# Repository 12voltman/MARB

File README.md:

# MARB
Manual Audio Routing Board for channel muxing

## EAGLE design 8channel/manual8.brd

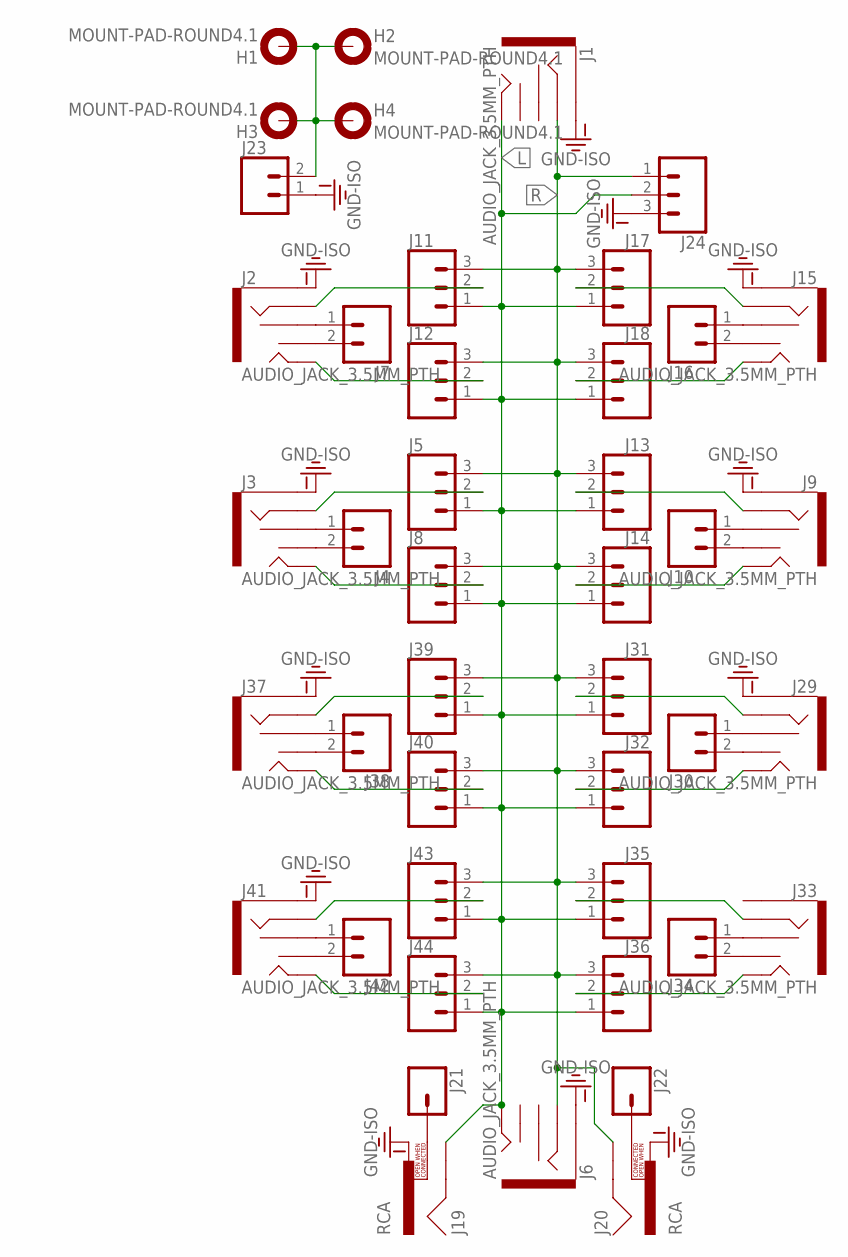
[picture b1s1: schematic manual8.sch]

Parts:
H1, H2, H3, H4: MOUNT-PAD-ROUND4.1; 4,1-PAD
J1, J2, J3, J6, J9, J15, J29, J33, J37, J41: AUDIO_JACK_3.5MM_PTH; AUDIO-JACK
J4, J7, J10, J16, J23, J30, J34, J38, J42: CONN_02; 1X02
J5, J8, J11, J12, J13, J14, J17, J18, J24, J31, J32, J35, J36, J39, J40, J43, J44: CONN_03; 1X03
J19, J20: RCA
J21, J22: CONN_01; 1X01

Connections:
GND-ISO: J1.SLEEVE, J2.SLEEVE, J3.SLEEVE, J6.SLEEVE, J9.SLEEVE, J15.SLEEVE, J19.PIN, J20.PIN, J23.1, J24.3, J29.SLEEVE, J33.SLEEVE, J37.SLEEVE, J41.SLEEVE
L: J1.TIP, J5.1, J6.TIP, J8.1, J11.1, J12.1, J13.1, J14.1, J17.1, J18.1, J19.SHELL, J24.2, J31.1, J32.1, J35.1, J36.1, J39.1, J40.1, J43.1, J44.1
unnamed: J2.RSH, J7.1
unnamed: J2.TSH, J7.2
unnamed: J2.RING, J11.2
unnamed: J2.TIP, J12.2
unnamed: J3.RSH, J4.1
unnamed: J3.TSH, J4.2
unnamed: J3.RING, J5.2
unnamed: J3.TIP, J8.2
unnamed: J9.RSH, J10.1
unnamed: J9.TSH, J10.2
unnamed: J9.RING, J13.2
unnamed: J9.TIP, J14.2
unnamed: J15.RSH, J16.1
unnamed: J15.TSH, J16.2
unnamed: J15.RING, J17.2
unnamed: J15.TIP, J18.2
unnamed: J19.SWITCH, J21.1
unnamed: J20.SWITCH, J22.1
unnamed: H1.B4,1, H2.B4,1, H3.B4,1, H4.B4,1, J23.2
unnamed: J29.RSH, J30.1
unnamed: J29.TSH, J30.2
unnamed: J29.RING, J31.2
unnamed: J29.TIP, J32.2
unnamed: J33.RSH, J34.1
unnamed: J33.TSH, J34.2
unnamed: J33.RING, J35.2
unnamed: J33.TIP, J36.2
unnamed: J37.RSH, J38.1
unnamed: J37.TSH, J38.2
unnamed: J37.RING, J39.2
unnamed: J37.TIP, J40.2
unnamed: J41.RSH, J42.1
unnamed: J41.TSH, J42.2
unnamed: J41.RING, J43.2
unnamed: J41.TIP, J44.2
R: J1.RING, J5.3, J6.RING, J8.3, J11.3, J12.3, J13.3, J14.3, J17.3, J18.3, J20.SHELL, J24.1, J31.3, J32.3, J35.3, J36.3, J39.3, J40.3, J43.3, J44.3

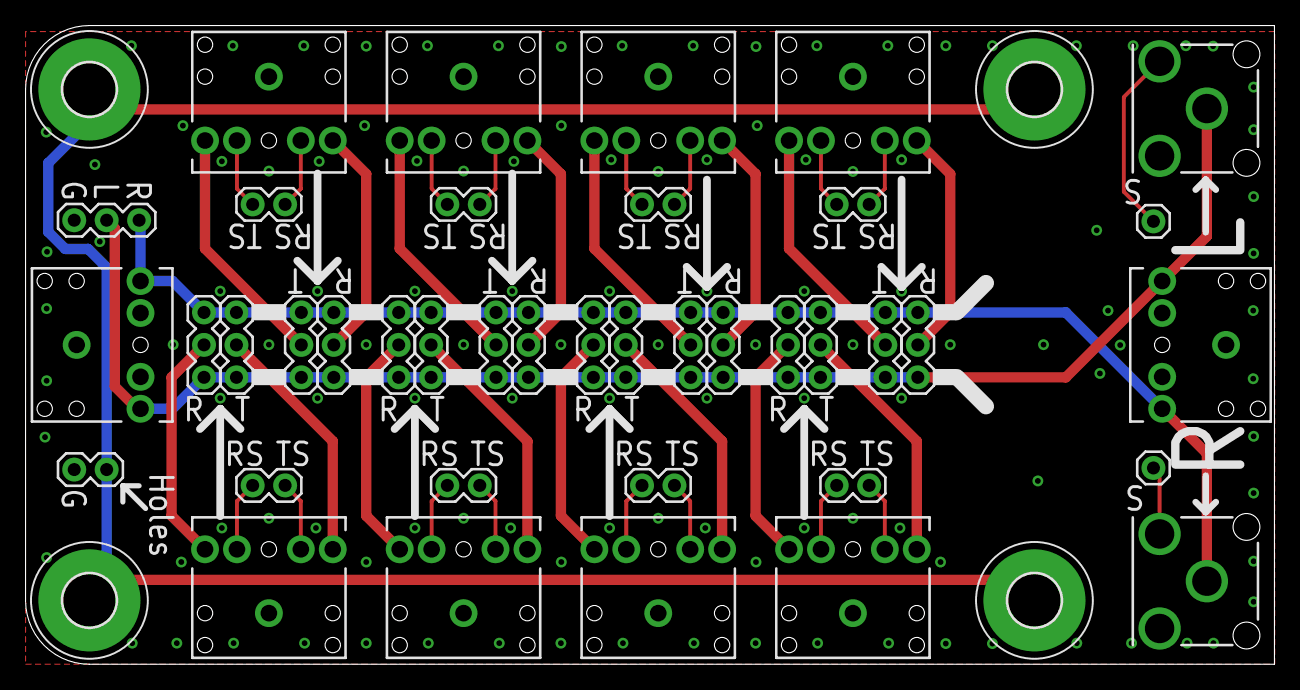
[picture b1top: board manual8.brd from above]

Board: 2 copper layers, 97.8 x 50.0 mm, 44 parts (0 on the bottom side), 38 nets.

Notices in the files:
parts and their libraries:
SparkFun-Connectors: Licensing: Creative Commons ShareAlike 4.0 International - https://creativecommons.org/licenses/by-sa/4.0
